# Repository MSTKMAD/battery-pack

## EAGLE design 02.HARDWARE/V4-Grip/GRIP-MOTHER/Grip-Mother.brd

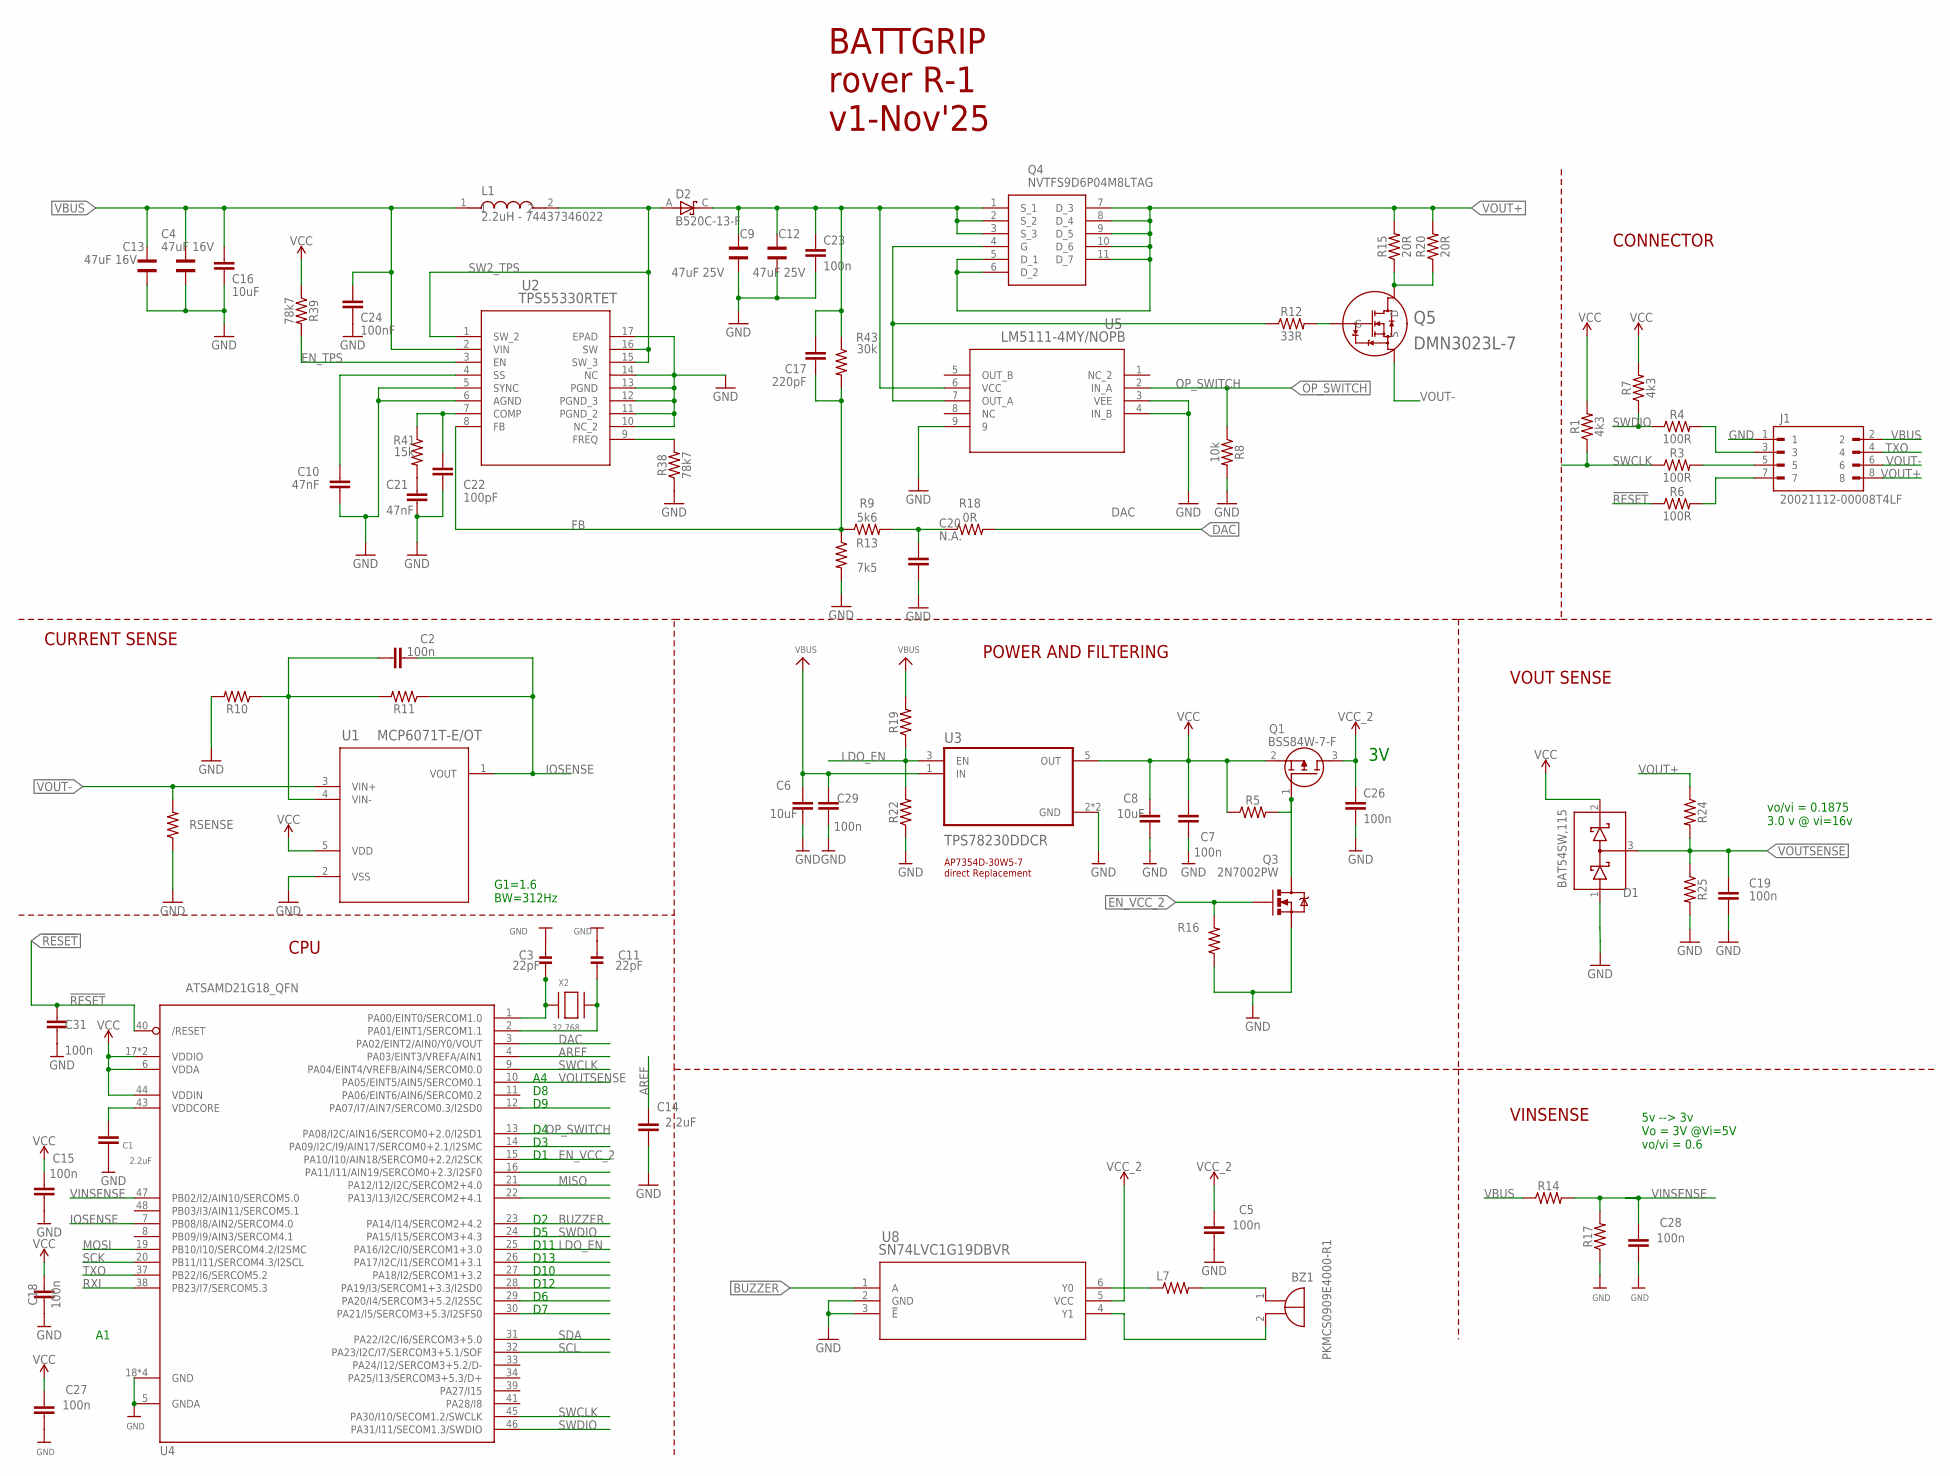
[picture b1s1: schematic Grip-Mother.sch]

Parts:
BZ1: PKMCS0909E4000-R1; PKMCS0909
C1, C14: 2.2uF; 0603
C2, C19, C23: 100n; 0603
C3, C11: 22pF; 0603-NO
C4, C13: 47uF 16V; WCAP-CSGP_1210
C5, C7, C15, C18, C26, C27, C28, C29, C31: 100n; 0402
C6, C8: 10uF; 0603
C9, C12: 47uF 25V; WCAP-CSGP_1210
C10, C21: 47nF; 0603
C16: 10uF; 0805
C17: 220pF; 0603
C20: N.A.; 0603
C22: 100pF; 0603
C24: 100nF; 0603
D1: BAT54SW,115; SOT65P210X110-3N
D2: B520C-13-F; DIOM7959X250N
J1: 20021112-00008T4LF; AMPHENOL_20021112-00008T4LF
L1: 2.2uH - 74437346022; INDM7366X500
L7: MMZ2012Y202BT000; 0805
Q1: BSS84W-7-F; SOT65P222X110-3N
Q3: 2N7002PW; SOT323
Q4: NVTFS9D6P04M8LTAG; NVTFS5124PLTWG
Q5: DMN3023L-7; SOT23-TO-236AB_NEX-L
R1, R7: 4k3; 0402
R3, R4, R6: 100R; 0402
R5, R10, R11, R14, R16, R17, R19, R22, R24, R25: 0402
R8: 10k; 0402
R9: 5k6; 0402
R12: 33R; 0402
R13: 7k5; 0402
R15, R20: 20R; 1206
R18: 0R; 0402
R38, R39: 78k7; 0402
R41: 15k; 0402
R43: 30k; 0402
RSENSE: 1206
U1: MCP6071T-E/OT; SOT-23-5_MC_MCH
U2: TPS55330RTET; RTE16_1P66X1P66_TEX
U3: TPS78230DDCR; SOT95P280X110-5N
U4: ATSAMD21G18_QFN; TQFN48_7MM
U5: LM5111-4MY/NOPB; MUY08A
U8: SN74LVC1G19DBVR; DBV6
X2: 32.768; XTAL3215

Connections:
!RESET: C31.1, R6.1, U4.40 (/RESET)
AREF: C14.1, U4.4 (PA03/EINT3/VREFA/AIN1)
BUZZER: U4.23 (PA14/I14/SERCOM2+4.2), U8.1 (A)
COMP_TPS: C22.2, R41.1, U2.7 (COMP)
DAC: R18.2, U4.3 (PA02/EINT2/AIN0/Y0/VOUT)
EN_TPS: R39.2, U2.3 (EN)
EN_VCC_2: Q3.1 (G), R16.2, U4.15 (PA10/I10/AIN18/SERCOM0+2.2/I2SCK)
FB: C17.1, R9.1, R13.1, R43.2, U2.8 (FB)
FREQ_TPS: R38.2, U2.9 (FREQ)
GND: C1.2, C3.2, C4.1, C5.2, C6.2, C7.2, C8.2, C9.1, C10.2, C11.2, C12.1, C13.1, C14.2, C15.2, C16.1, C18.2, C19.2, C20.2, C21.1, C22.1, C23.2, C24.1, C26.2, C27.2, C28.2, C29.2, C31.2, D1.1 (A), J1.1, Q3.2 (S), R8.2, R10.2, R13.2, R16.1, R17.1, R22.1, R25.2, R38.1, RSENSE.1, U1.2 (VSS), U2.5 (SYNC), U2.6 (AGND), U2.10 (NC_2), U2.11 (PGND_2), U2.12 (PGND_3), U2.13 (PGND), U2.14 (NC), U2.17 (EPAD), U3.2 (GND), U3.4 (GND), U4.5 (GNDA), U4.18 (GND), U4.35 (GND), U4.42 (GND), U4.THERMAL (GND), U5.3 (VEE), U5.4 (IN_B), U5.9, U8.2 (GND), U8.3 (!E)
IOSENSE: C2.1, R11.1, U1.1 (VOUT), U4.7 (PB08/I8/AIN2/SERCOM4.0)
LDO_EN: R19.1, R22.2, U3.3 (EN), U4.25 (PA16/I2C/I0/SERCOM1+3.0)
MISO: U4.21 (PA12/I12/I2C/SERCOM2+4.0)
MOSI: U4.19 (PB10/I10/SERCOM4.2/I2SMC)
unnamed: Q4.4 (G), R12.1, U5.7 (OUT_A)
unnamed: J1.7, R6.2
unnamed: J1.5, R3.2
unnamed: C2.2, R10.1, R11.2, U1.4 (VIN-)
unnamed: Q1.1 (G), Q3.3 (D), R5.2
unnamed: Q5.3 (D), R15.1, R20.1
unnamed: C3.1, U4.1 (PA00/EINT0/SERCOM1.0), X2.P$1
unnamed: C11.1, U4.2 (PA01/EINT1/SERCOM1.1), X2.P$2
unnamed: J1.3, R4.2
unnamed: C20.1, R9.2, R18.1
unnamed: Q5.1 (G), R12.2
unnamed: L7.1, U8.6 (Y0)
unnamed: BZ1.1 (+), L7.2
unnamed: BZ1.2 (-), U8.4 (Y1)
unnamed: C10.1, U2.4 (SS)
unnamed: C21.2, R41.2
OP_SWITCH: R8.1, U4.13 (PA08/I2C/AIN16/SERCOM0+2.0/I2SD1), U5.2 (IN_A)
RXI: U4.38 (PB23/I7/SERCOM5.3)
SCK: U4.20 (PB11/I11/SERCOM4.3/I2SCL)
SCL: U4.32 (PA23/I2C/I7/SERCOM3+5.1/SOF)
SDA: U4.31 (PA22/I2C/I6/SERCOM3+5.0)
SW2_TPS: D2.A, L1.2, U2.1 (SW_2), U2.15 (SW_3), U2.16 (SW)
SWCLK: R1.1, R3.1, U4.9 (PA04/EINT4/VREFB/AIN4/SERCOM0.0), U4.45 (PA30/I10/SECOM1.2/SWCLK)
SWDIO: R4.1, R7.1, U4.24 (PA15/I15/SERCOM3+4.3), U4.46 (PA31/I11/SECOM1.3/SWDIO)
TXO: J1.4, U4.37 (PB22/I6/SERCOM5.2)
VBUS: C4.2, C6.1, C13.2, C16.2, C24.2, C29.1, J1.2, L1.1, R14.1, R19.2, U2.2 (VIN), U3.1 (IN)
VCC: C7.1, C8.1, C15.1, C18.1, C27.1, D1.2 (C), Q1.2 (S), R1.2, R5.1, R7.2, R39.1, U1.5 (VDD), U3.5 (OUT), U4.6 (VDDA), U4.17 (VDDIO), U4.36 (VDDIO), U4.44 (VDDIN)
VCC_2: C5.1, C26.1, Q1.3 (D), U8.5 (VCC)
VDDCORE1: C1.1, U4.43 (VDDCORE)
VINSENSE: C28.1, R14.2, R17.2, U4.47 (PB02/I2/AIN10/SERCOM5.0)
VOUT+: J1.8, Q4.5 (D_1), Q4.6 (D_2), Q4.7 (D_3), Q4.8 (D_4), Q4.9 (D_5), Q4.10 (D_6), Q4.11 (D_7), R15.2, R20.2, R24.1
VOUT-: J1.6, Q5.2 (S), RSENSE.2, U1.3 (VIN+)
VOUTSENSE: C19.1, D1.3 (A-C), R24.2, R25.1, U4.10 (PA05/EINT5/AIN5/SERCOM0.1)
VSOURCE: C9.2, C12.2, C17.2, C23.1, D2.C, Q4.1 (S_1), Q4.2 (S_2), Q4.3 (S_3), R43.1, U5.6 (VCC)

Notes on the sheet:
POWER AND FILTERING
AP7354D-30W5-7 direct Replacement
CURRENT SENSE
5v --> 3v Vo = 3V @Vi=5V vo/vi = 0.6
BATTGRIP rover R-1 v1-Nov'25
VINSENSE
G1=1.6 BW=312Hz
vo/vi = 0.1875 3.0 v @ vi=16v
CONNECTOR
D10
CPU
D13
D11
D12
VOUT SENSE

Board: 4 copper layers, 73 parts (43 on the bottom side), 42 nets, no tracks yet.

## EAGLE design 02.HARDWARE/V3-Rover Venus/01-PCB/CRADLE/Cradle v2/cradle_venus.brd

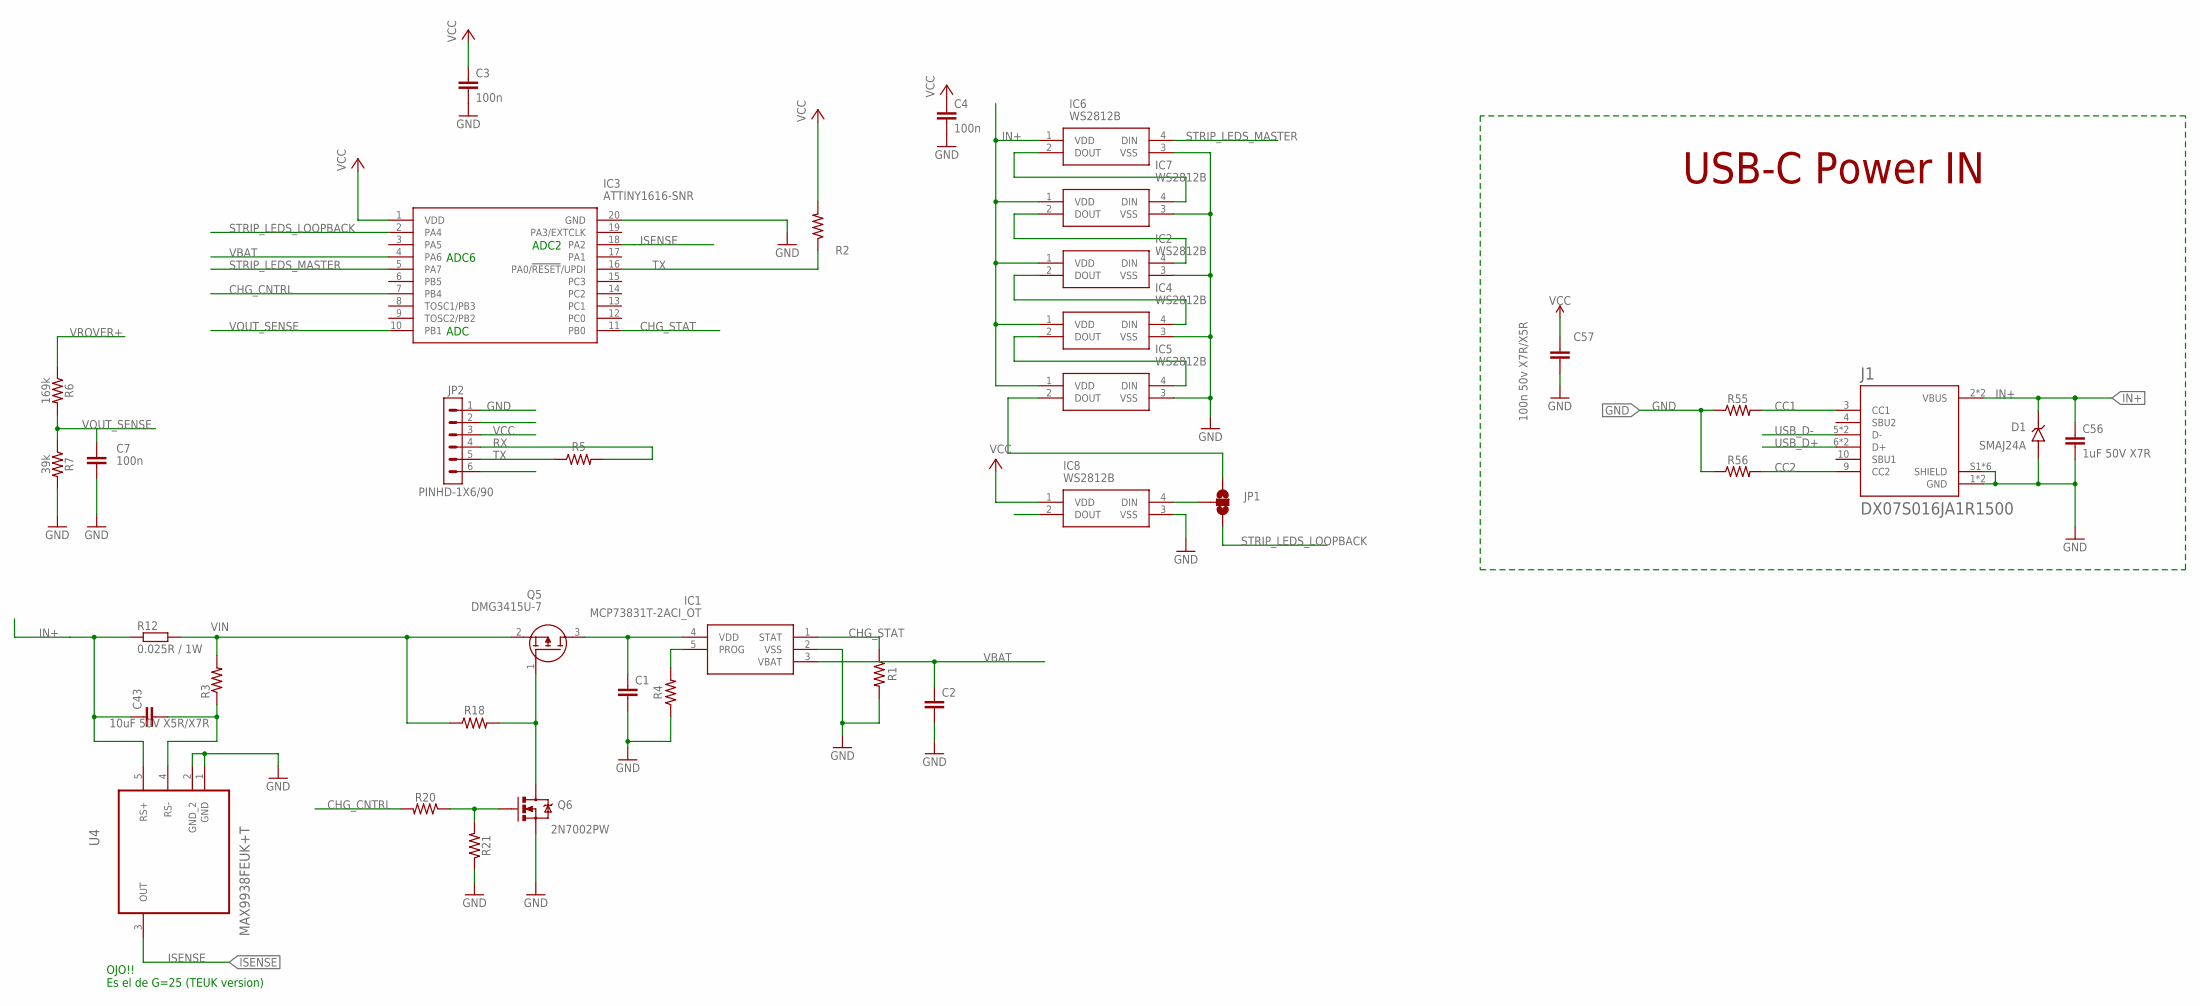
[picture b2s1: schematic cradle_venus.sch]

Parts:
C1, C2: C-EUC0805; C0805
C3, C4: 100n; C0805
C7: 100n; 0603
C43: 10uF 50V X5R/X7R; 1206
C56: 1uF 50V X7R; 0805
C57: 100n 50v X7R/X5R; 0805
D1: SMAJ24A; DIOM4325X244N
IC1: MCP73831T-2ACI_OT; SOT95P270X145-5N
IC2, IC4, IC5, IC6, IC7, IC8: WS2812B
IC3: ATTINY1616-SNR; SOIC127P1030X265-20N
J1: DX07S016JA1R1500; JAE_DX07S016JA1R1500
JP1: JUMPER-SMT_3_NO_SILK; SMT-JUMPER_3_NO_SILK
JP2: PINHD-1X6/90; 1X06/90
Q5: DMG3415U-7; SSM3J332RLFT
Q6: 2N7002PW; SOT323
R1, R2, R3, R4, R5, R18, R20, R21, R55, R56: 0805
R6: 169k; 0603
R7: 39k; 0603
R12: 0.025R / 1W; R2512
U4: MAX9938FEUK+T; SOT95P280X145-5N

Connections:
CC1: J1.3 (CC1), R55.2
CC2: J1.9 (CC2), R56.2
CHG_CNTRL: IC3.7 (PB4), R20.2
CHG_STAT: IC1.1 (STAT), IC3.11 (PB0), R1.1
GND: C1.2, C2.2, C3.2, C4.2, C7.2, C56.2, C57.2, D1.A, IC1.2 (VSS), IC2.3 (VSS), IC3.20 (GND), IC4.3 (VSS), IC5.3 (VSS), IC6.3 (VSS), IC7.3 (VSS), IC8.3 (VSS), J1.1 (GND), J1.12 (GND), J1.S1 (SHIELD), J1.S2 (SHIELD), J1.S3 (SHIELD), J1.S4 (SHIELD), J1.S5 (SHIELD), J1.S6 (SHIELD), JP2.1, Q6.2 (S), R1.2, R4.1, R7.2, R21.1, R55.1, R56.1, U4.1 (GND), U4.2 (GND_2)
IN+: C3.1, C4.1, C43.1, C56.1, C57.1, D1.C (K), IC2.1 (VDD), IC3.1 (VDD), IC4.1 (VDD), IC5.1 (VDD), IC6.1 (VDD), IC7.1 (VDD), IC8.1 (VDD), J1.2 (VBUS), J1.11 (VBUS), R2.2, R12.1, U4.5 (RS+)
ISENSE: IC3.18 (PA2), U4.3 (OUT)
unnamed: C1.1, IC1.4 (VDD), Q5.3 (D)
unnamed: IC6.2 (DOUT), IC7.4 (DIN)
unnamed: C43.2, R3.1, U4.4 (RS-)
unnamed: IC2.2 (DOUT), IC4.4 (DIN)
unnamed: IC4.2 (DOUT), IC5.4 (DIN)
unnamed: Q6.1 (G), R20.1, R21.2
unnamed: IC2.4 (DIN), IC7.2 (DOUT)
unnamed: IC8.4 (DIN), JP1.2
unnamed: IC5.2 (DOUT), JP1.1
unnamed: Q5.1 (G), Q6.3 (D), R18.2
unnamed: IC1.5 (PROG), R4.2
RX: JP2.4, R5.2
STRIP_LEDS_LOOPBACK: IC3.2 (PA4), JP1.3
STRIP_LEDS_MASTER: IC3.5 (PA7), IC6.4 (DIN)
TX: IC3.16 (PA0/!RESET!/UPDI), JP2.5, R2.1, R5.1
USB_D+: J1.6 (D+), J1.7 (D+)
USB_D-: J1.5 (D-), J1.8 (D-)
VBAT: C2.1, IC1.3 (VBAT), IC3.4 (PA6)
VCC: JP2.3
VIN: Q5.2 (S), R3.2, R12.2, R18.1
VOUT_SENSE: C7.1, IC3.10 (PB1), R6.2, R7.1
VROVER+: R6.1

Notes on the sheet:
USB-C Power IN
OJO!! Es el de G=25 (TEUK version)
ADC2
ADC
ADC6

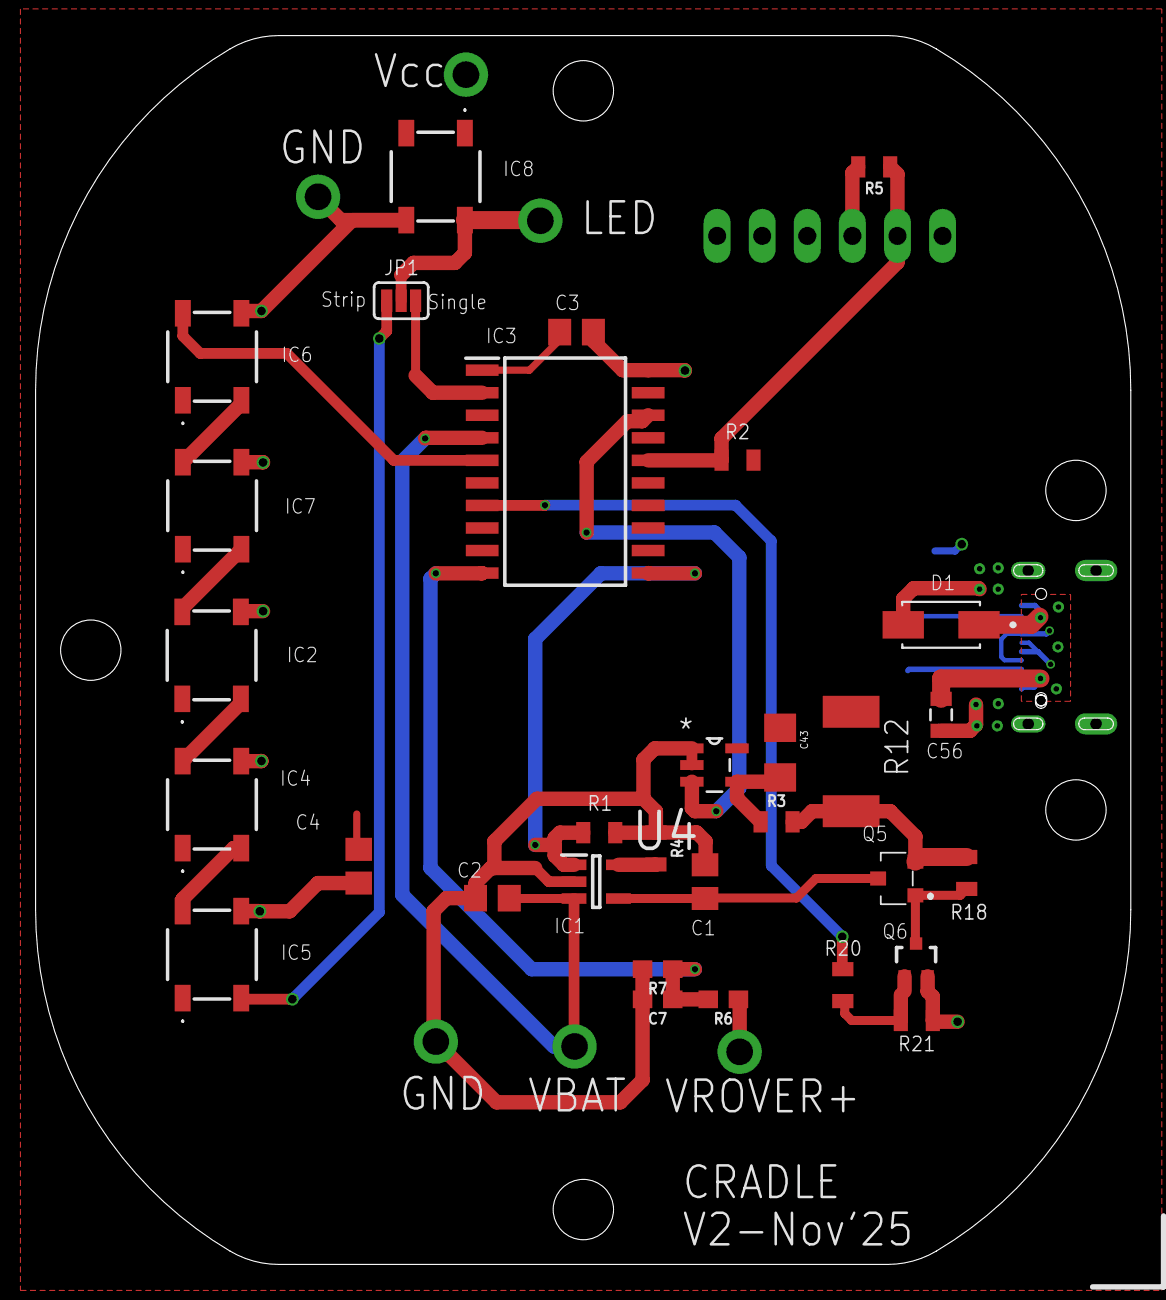
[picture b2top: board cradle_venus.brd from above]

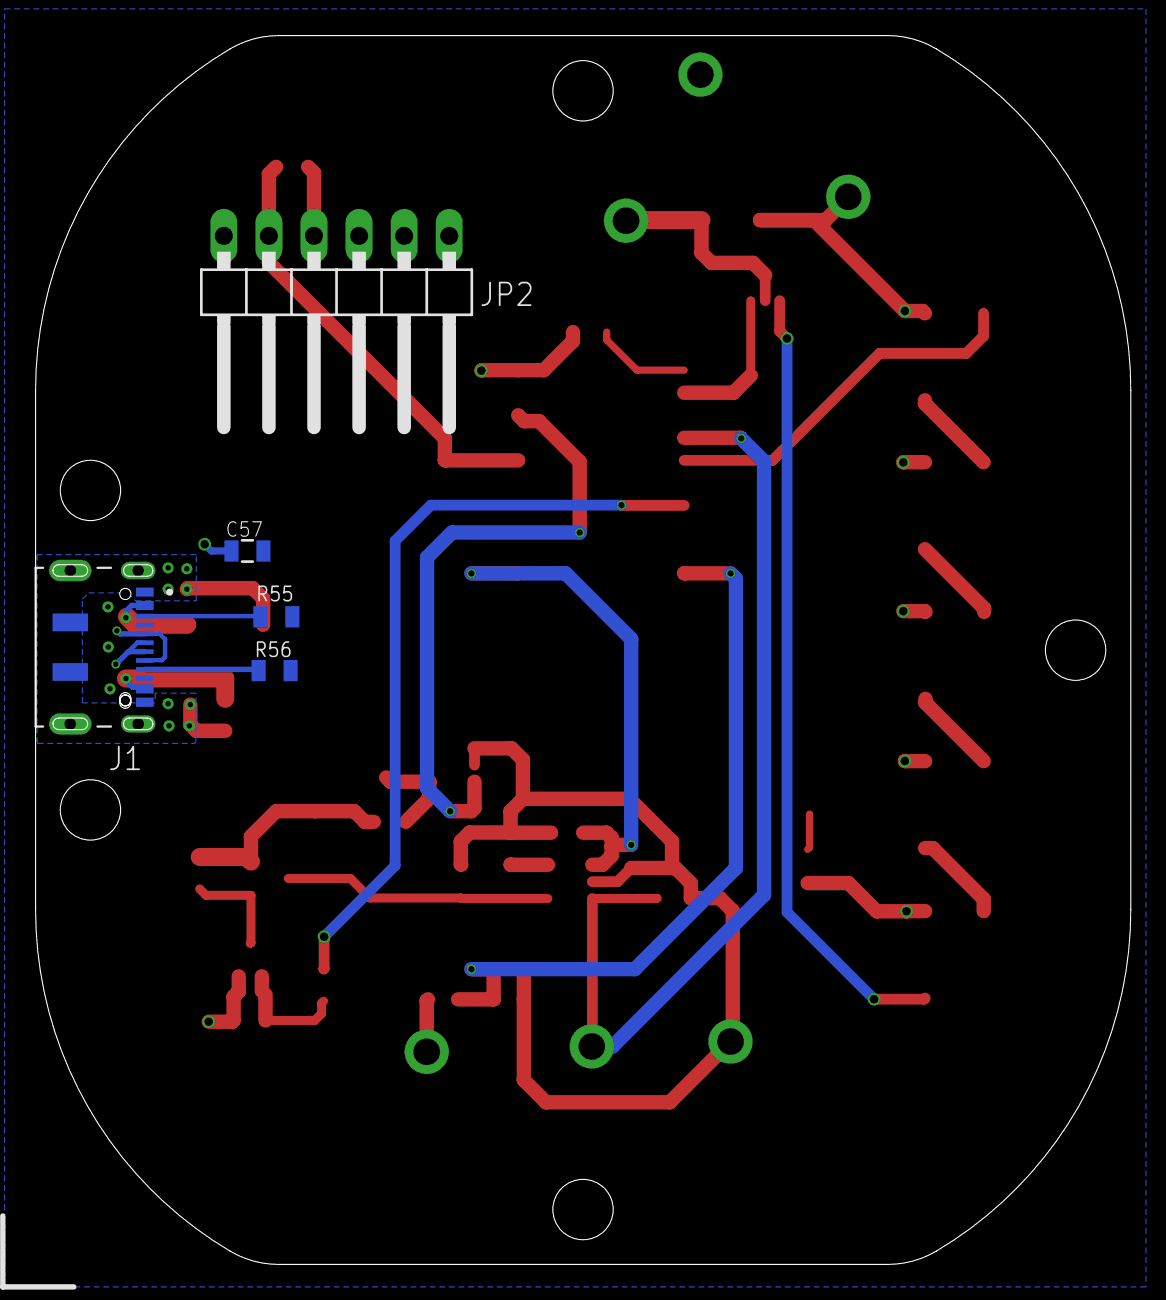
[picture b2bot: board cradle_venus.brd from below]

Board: 2 copper layers, 61.7 x 69.2 mm, 36 parts (5 on the bottom side), 27 nets.

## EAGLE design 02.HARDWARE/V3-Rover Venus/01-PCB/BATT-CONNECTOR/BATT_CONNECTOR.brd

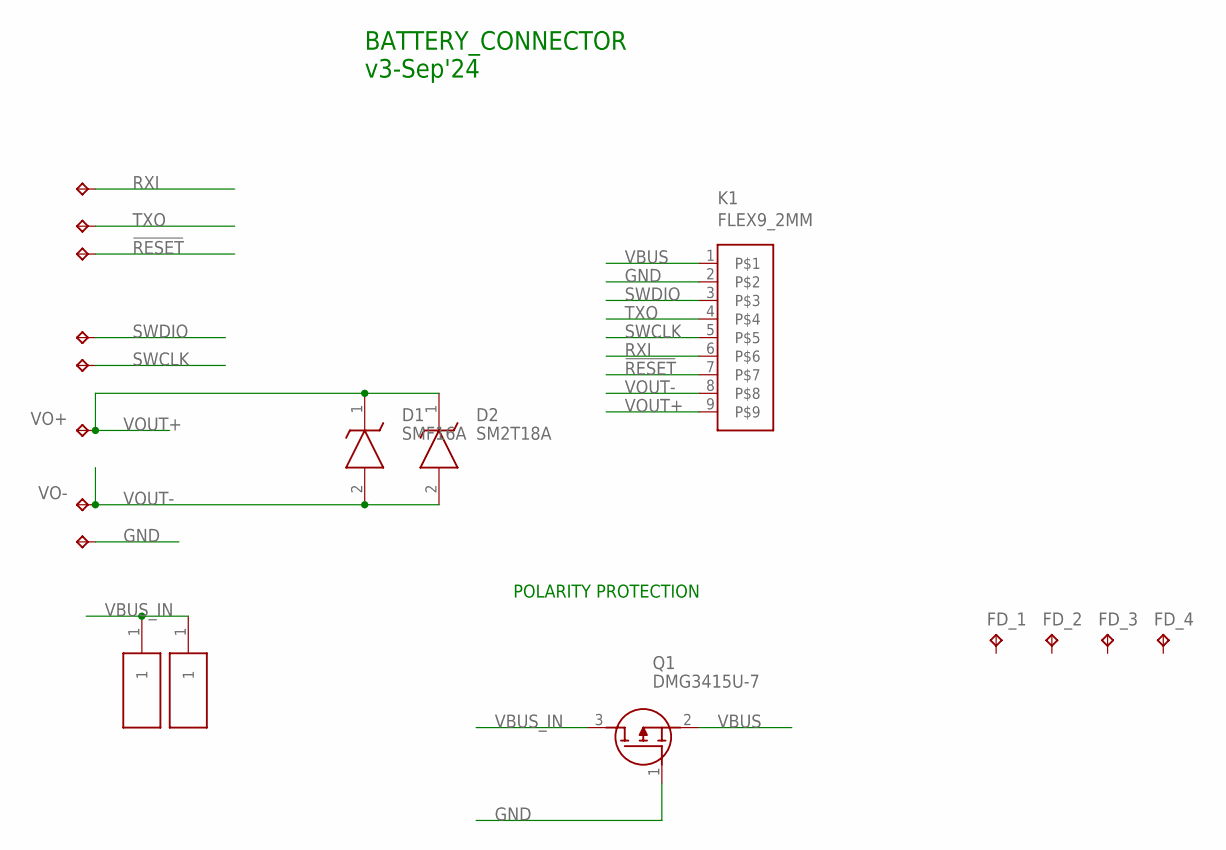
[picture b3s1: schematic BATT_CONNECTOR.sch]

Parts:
!RESET: TPB2,54; B2,54
D1: SMF16A; SODFL3618X110N
D2: SM2T18A
FD_1, FD_2, FD_3, FD_4: FD_1; TP06SQ
GND: TPB2,54; B2,54
H1, H2: S1761-42R; S176142R
K1: FLEX9_2MM
Q1: DMG3415U-7; SSM3J332RLFT
RXI: TPB2,54; B2,54
SWCLK: TPB2,54; B2,54
SWDIO: TPB2,54; B2,54
TXO: TPB2,54; B2,54
VO+: TPB2,54; B2,54
VO-: TPB2,54; B2,54

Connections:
!RESET: !RESET.TP, K1.7
GND: GND.TP, K1.2, Q1.1 (G)
RXI: K1.6, RXI.TP
SWCLK: K1.5, SWCLK.TP
SWDIO: K1.3, SWDIO.TP
TXO: K1.4, TXO.TP
VBUS: K1.1, Q1.2 (S)
VBUS_IN: H1.1, H2.1, Q1.3 (D)
VOUT+: D1.1 (K), D2.1 (K), K1.9, VO+.TP
VOUT-: D1.2 (A), D2.2 (A), K1.8, VO-.TP

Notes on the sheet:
POLARITY PROTECTION
BATTERY_CONNECTOR v3-Sep'24

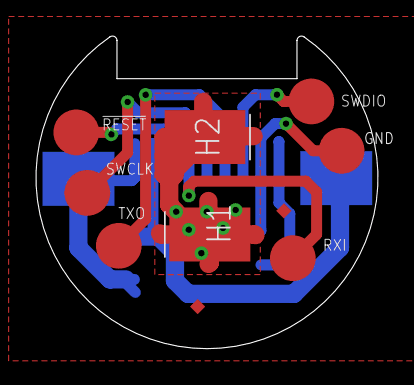
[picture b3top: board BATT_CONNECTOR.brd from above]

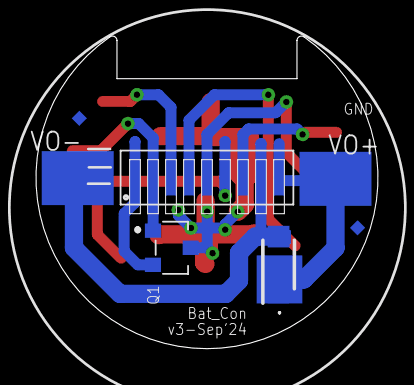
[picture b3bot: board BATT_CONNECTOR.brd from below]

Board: 4 copper layers, 19.0 x 17.4 mm, 18 parts (8 on the bottom side), 10 nets.

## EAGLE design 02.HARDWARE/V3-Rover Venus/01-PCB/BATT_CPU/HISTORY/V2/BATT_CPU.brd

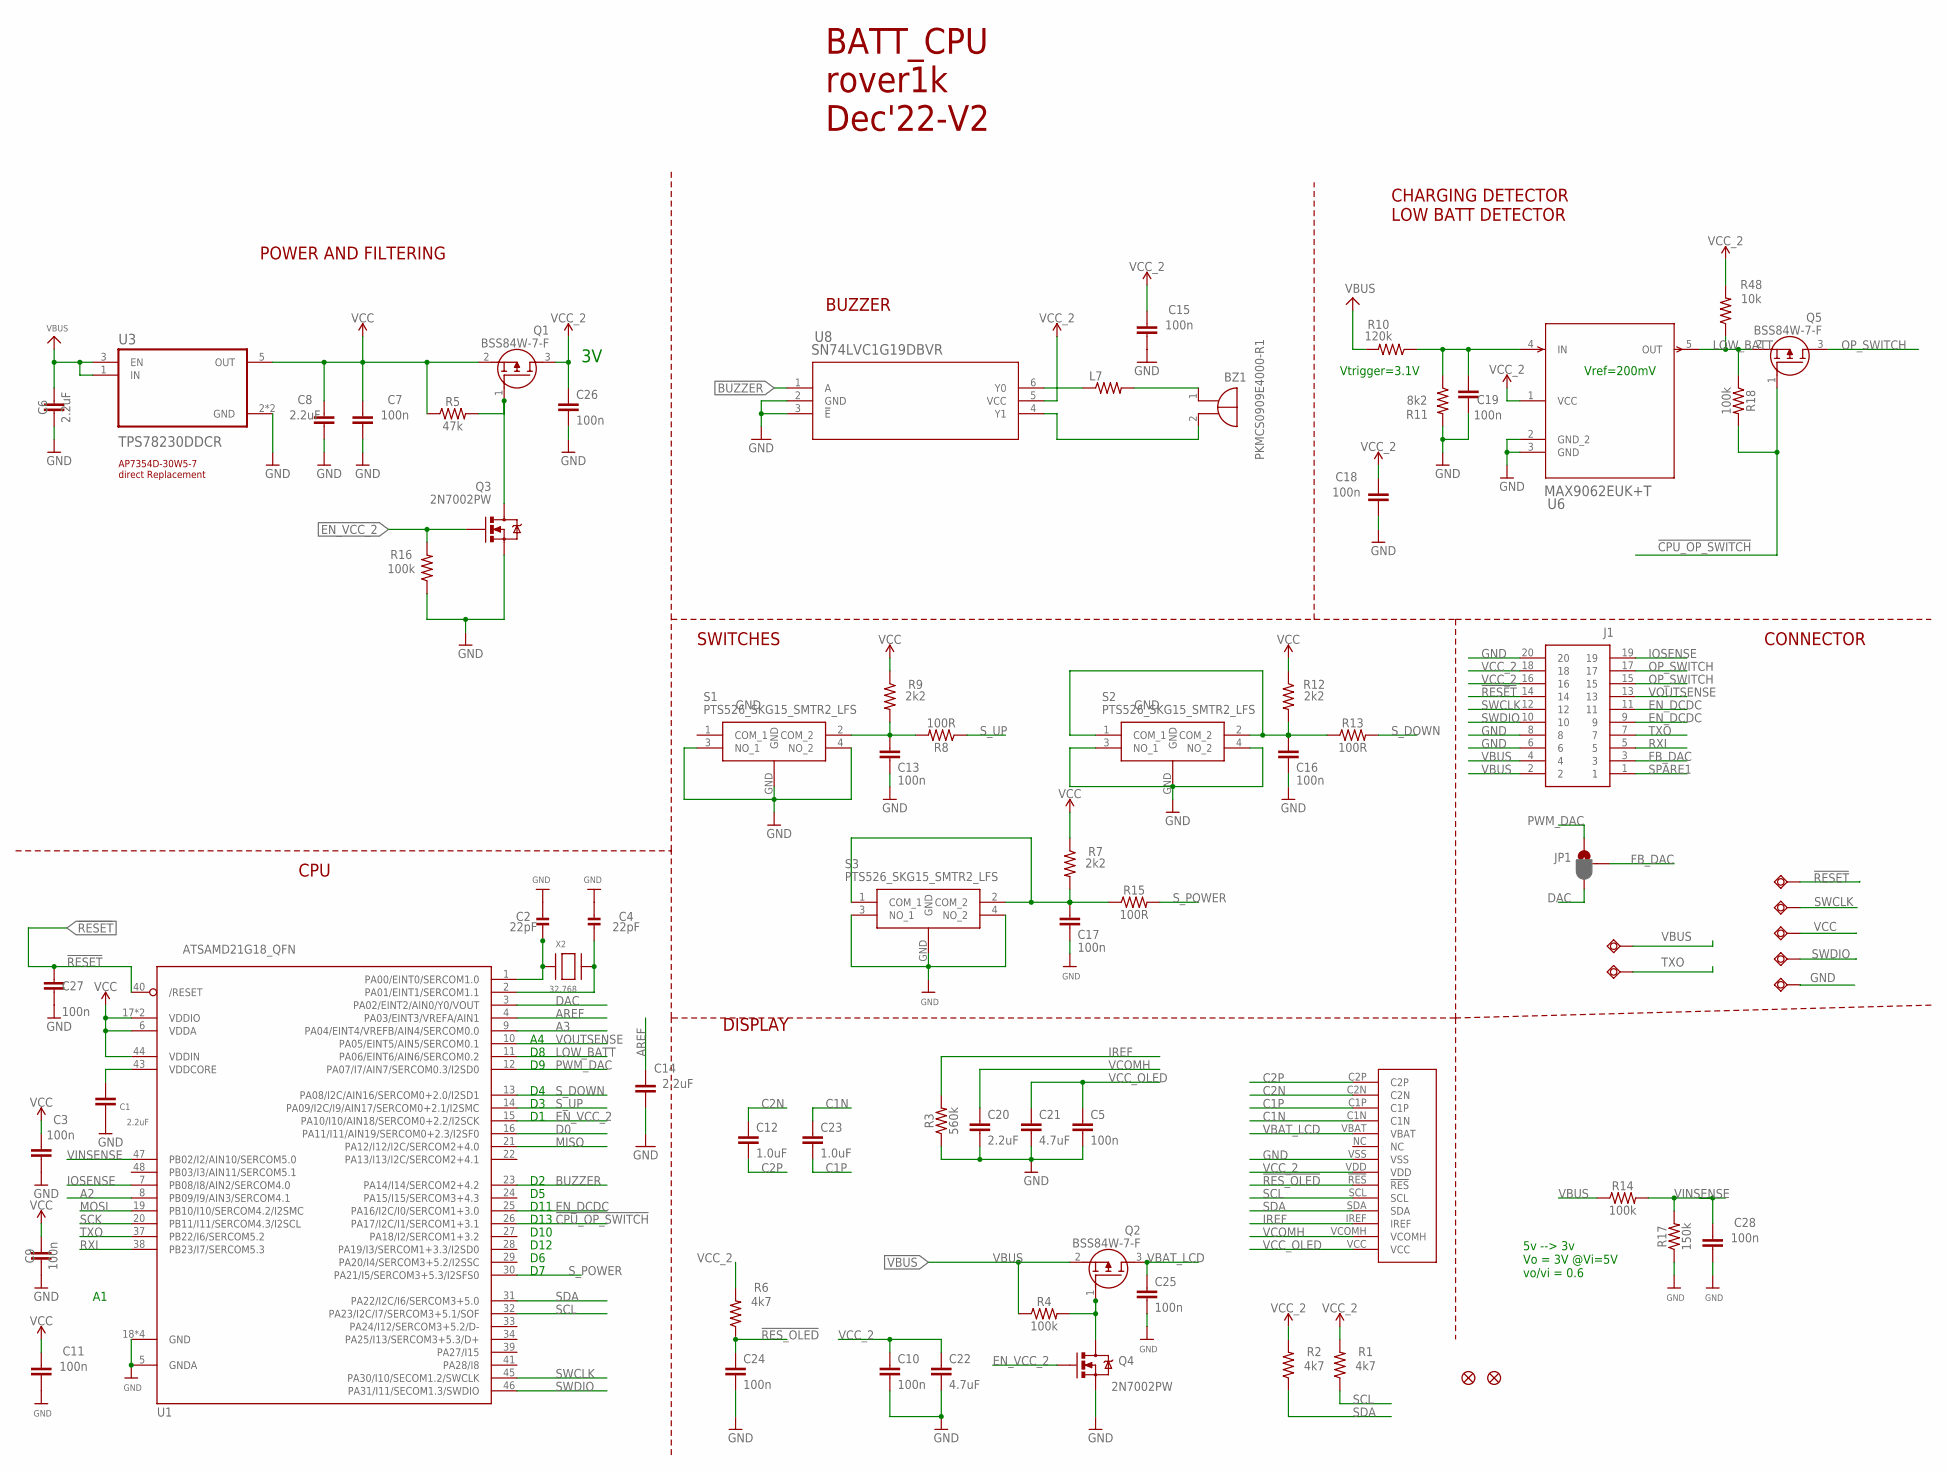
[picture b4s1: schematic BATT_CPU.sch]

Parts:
BZ1: PKMCS0909E4000-R1; PKMCS0909
C1, C6, C8, C14, C20: 2.2uF; 0603
C2, C4: 22pF; 0603-NO
C3, C5, C7, C9, C10, C11, C13, C15, C16, C17, C18, C19, C24, C25, C26, C27, C28: 100n; 0402
C12, C23: 1.0uF; 0402
C21, C22: 4.7uF; 0603
J1: DF40C_2.0_-20DS-0.4V_51_; DF40C2020DS04V51
JP1: JUMPER-SMT_3_1-NC_PASTE_SILK; SMT-JUMPER_3_1-NC_PASTE_SILK
L7: MMZ2012Y202BT000; 0805
Q1, Q2, Q5: BSS84W-7-F; SOT65P222X110-3N
Q3, Q4: 2N7002PW; SOT323
R1, R2, R6: 4k7; 0402
R3: 560k; 0402
R4, R14, R16, R18: 100k; 0402
R5: 47k; 0402
R7, R9, R12: 2k2; 0402
R8, R13, R15: 100R; 0402
R10: 120k; 0402
R11: 8k2; 0402
R17: 150k; 0402
R48: 10k; 0402
S1, S2, S3: PTS526_SKG15_SMTR2_LFS; PTS526SKG15SMTR2LFS
U1: ATSAMD21G18_QFN; TQFN48_7MM
U3: TPS78230DDCR; SOT95P280X110-5N
U6: MAX9062EUK+T; 21-0057F_MXM
U8: SN74LVC1G19DBVR; DBV6
U$30: 64X32_OLED_049; LCD_14_PINS
U$34, U$35: FIDUCIAL""; FIDUCIAL_1MM
VBUS, VBUS1, VBUS2, VBUS3, VBUS4, VBUS5, VBUS6: TESTPAD_TPSQB1,27; TESTPAD_B1,27
X2: 32.768; XTAL3215

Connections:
!CPU_OP_SWITCH: Q5.1 (G), R18.2, U1.26 (PA17/I2C/I1/SERCOM1+3.1)
!RESET: C27.1, J1.14, U1.40 (/RESET), VBUS1.TP
!RES_OLED: C24.1, R6.1, U$30.!RES
A2: U1.8 (PB09/I9/AIN3/SERCOM4.1)
A3: U1.9 (PA04/EINT4/VREFB/AIN4/SERCOM0.0)
AREF: C14.1, U1.4 (PA03/EINT3/VREFA/AIN1)
BUZZER: U1.23 (PA14/I14/SERCOM2+4.2), U8.1 (A)
C1N: C23.1, U$30.C1N
C1P: C23.2, U$30.C1P
C2N: C12.1, U$30.C2N
C2P: C12.2, U$30.C2P
D0: U1.16 (PA11/I11/AIN19/SERCOM0+2.3/I2SF0)
DAC: JP1.3, U1.3 (PA02/EINT2/AIN0/Y0/VOUT)
EN_DCDC: J1.9, J1.11, U1.25 (PA16/I2C/I0/SERCOM1+3.0)
EN_VCC_2: Q3.1 (G), Q4.1 (G), R16.2, U1.15 (PA10/I10/AIN18/SERCOM0+2.2/I2SCK)
FB_DAC: J1.3, JP1.2
GND: C1.2, C2.2, C3.2, C4.2, C5.2, C6.2, C7.2, C8.2, C9.2, C10.2, C11.2, C13.2, C14.2, C15.2, C16.2, C17.2, C18.2, C19.2, C20.2, C21.2, C22.2, C24.2, C25.2, C26.2, C27.2, C28.2, J1.6, J1.8, J1.20, Q3.2 (S), Q4.2 (S), R3.1, R11.2, R16.1, R17.1, S1.3 (NO_1), S1.4 (NO_2), S1.GND, S2.3 (NO_1), S2.4 (NO_2), S2.GND, S3.3 (NO_1), S3.4 (NO_2), S3.GND, U1.5 (GNDA), U1.18 (GND), U1.35 (GND), U1.42 (GND), U1.THERMAL (GND), U3.2 (GND), U3.4 (GND), U6.2 (GND_2), U6.3 (GND), U8.2 (GND), U8.3 (!E), U$30.VSS, VBUS4.TP
IOSENSE: J1.19, U1.7 (PB08/I8/AIN2/SERCOM4.0)
IREF: R3.2, U$30.IREF
LOW_BATT: Q5.2 (S), R18.1, R48.1, U1.11 (PA06/EINT6/AIN6/SERCOM0.2), U6.5 (OUT)
MISO: U1.21 (PA12/I12/I2C/SERCOM2+4.0)
MOSI: U1.19 (PB10/I10/SERCOM4.2/I2SMC)
unnamed: C17.1, R7.2, R15.1, S3.1 (COM_1), S3.2 (COM_2)
unnamed: C13.1, R8.2, R9.2, S1.2 (COM_2)
unnamed: C16.1, R12.2, R13.1, S2.1 (COM_1), S2.2 (COM_2)
unnamed: Q2.1 (G), Q4.3 (D), R4.2
unnamed: C2.1, U1.1 (PA00/EINT0/SERCOM1.0), X2.P$1
unnamed: Q1.1 (G), Q3.3 (D), R5.2
unnamed: C4.1, U1.2 (PA01/EINT1/SERCOM1.1), X2.P$2
unnamed: C19.1, R10.1, R11.1, U6.4 (IN)
unnamed: L7.1, U8.6 (Y0)
unnamed: BZ1.1 (+), L7.2
unnamed: BZ1.2 (-), U8.4 (Y1)
OP_SWITCH: J1.15, J1.17, Q5.3 (D)
PWM_DAC: JP1.1, U1.12 (PA07/I7/AIN7/SERCOM0.3/I2SD0)
RXI: J1.5, U1.38 (PB23/I7/SERCOM5.3)
SCK: U1.20 (PB11/I11/SERCOM4.3/I2SCL)
SCL: R1.1, U1.32 (PA23/I2C/I7/SERCOM3+5.1/SOF), U$30.SCL
SDA: R2.1, U1.31 (PA22/I2C/I6/SERCOM3+5.0), U$30.SDA
SPARE1: J1.1
SWCLK: J1.12, U1.45 (PA30/I10/SECOM1.2/SWCLK), VBUS2.TP
SWDIO: J1.10, U1.46 (PA31/I11/SECOM1.3/SWDIO), VBUS3.TP
S_DOWN: R13.2, U1.13 (PA08/I2C/AIN16/SERCOM0+2.0/I2SD1)
S_POWER: R15.2, U1.30 (PA21/I5/SERCOM3+5.3/I2SFS0)
S_UP: R8.1, U1.14 (PA09/I2C/I9/AIN17/SERCOM0+2.1/I2SMC)
TXO: J1.7, U1.37 (PB22/I6/SERCOM5.2), VBUS6.TP
VBAT_LCD: C25.1, Q2.3 (D), U$30.VBAT
VBUS: C6.1, J1.2, J1.4, Q2.2 (S), R4.1, R10.2, R14.1, U3.1 (IN), U3.3 (EN), VBUS5.TP
VCC: C3.1, C7.1, C8.1, C9.1, C11.1, Q1.2 (S), R5.1, R7.1, R9.1, R12.1, R48.2, U1.6 (VDDA), U1.17 (VDDIO), U1.36 (VDDIO), U1.44 (VDDIN), U3.5 (OUT), VBUS.TP
VCC_2: C10.1, C15.1, C18.1, C22.1, C26.1, J1.16, J1.18, Q1.3 (D), R1.2, R2.2, R6.2, U6.1 (VCC), U8.5 (VCC), U$30.VDD
VCC_OLED: C5.1, C21.1, U$30.VCC
VCOMH: C20.1, U$30.VCOMH
VDDCORE: C1.1, U1.43 (VDDCORE)
VINSENSE: C28.1, R14.2, R17.2, U1.47 (PB02/I2/AIN10/SERCOM5.0)
VOUTSENSE: J1.13, U1.10 (PA05/EINT5/AIN5/SERCOM0.1)

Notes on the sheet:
POWER AND FILTERING
BUZZER
AP7354D-30W5-7 direct Replacement
D10
CHARGING DETECTOR LOW BATT DETECTOR
CPU
Vref=200mV
Vtrigger=3.1V
D13
D11
D12
5v --> 3v Vo = 3V @Vi=5V vo/vi = 0.6
BATT_CPU rover1k Dec'22-V2
DISPLAY
SWITCHES
CONNECTOR

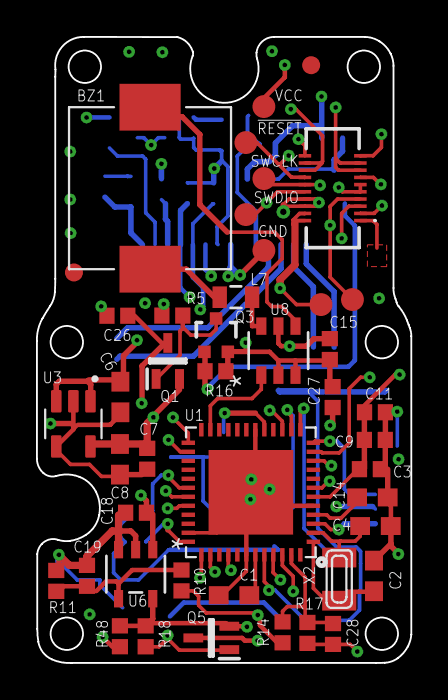
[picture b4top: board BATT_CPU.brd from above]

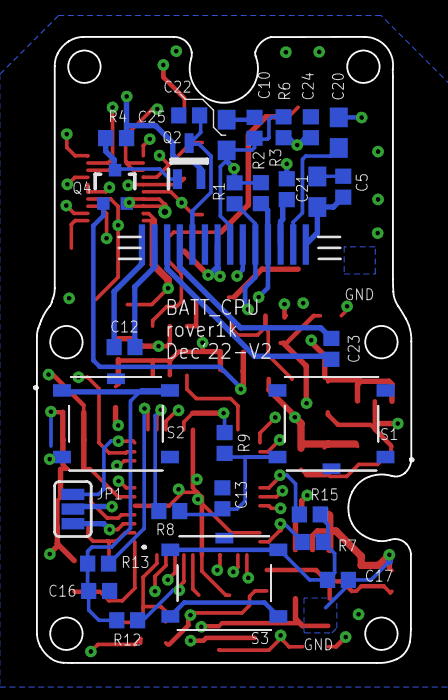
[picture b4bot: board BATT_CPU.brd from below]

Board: 4 copper layers, 20.8 x 34.8 mm, 74 parts (30 on the bottom side), 48 nets.

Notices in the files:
parts and their libraries:
SparkFun-Resistors: Licensing: Creative Commons ShareAlike 4.0 International - https://creativecommons.org/licenses/by-sa/4.0
microbuilder: This work is placed in the public domain, and may be freely used for commercial and non-commercial work with the following conditions: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
